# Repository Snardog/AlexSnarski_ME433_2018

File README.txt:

Alex Snarski
3/28/17
Hello World!

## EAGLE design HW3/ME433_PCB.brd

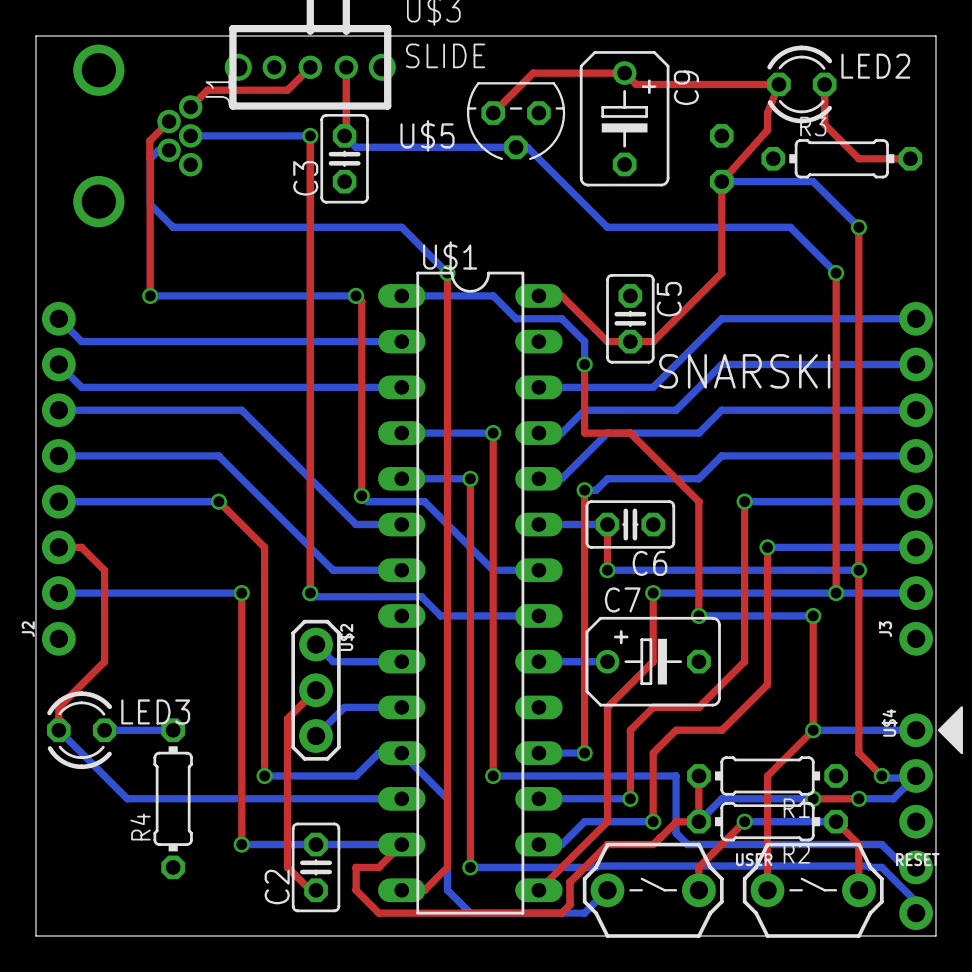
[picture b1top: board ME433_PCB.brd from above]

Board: 2 copper layers, 50.0 x 50.0 mm, 23 parts (1 on the bottom side), 27 nets.

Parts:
C2, C3, C4, C5, C6: 0.1uF; C025-025X050
C7, C9: 10uF; B45181B
J1: USB-MB-H
J2, J3: 1X08
LED2: RED; LED3MM
LED3: GREEN; LED3MM
R1, R2: 10k; 0204/7
R3, R4: 330; 0204/7
RESET: PB
U$1: PIC32; DIL28-3
U$2: OSC
U$3: SLIDE
U$4: PICKIT; 1X05
U$5: MCP1702; TO92
USER: PB

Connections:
+3V3: C2.2, C4.2, C5.2, C6.2, C9.+, J2.2, LED2.A, R1.2, R2.2, U$1.13, U$1.23, U$1.28, U$4.2, U$5.3
+5V: C3.2, J3.2, U$1.15, U$3.3, U$5.2
A0: J2.8, U$1.2
A1: J2.7, U$1.3
A4/LED: J2.3, LED3.A, U$1.12
B2: J2.6, U$1.6
B3: J2.5, U$1.7
B4/USER: J2.4, U$1.11, USER.1
B7: J3.3, U$1.16
B8: J3.4, U$1.17
B9: J3.5, U$1.18
B13: J3.6, U$1.24
B14: J3.7, U$1.25
B15: J3.8, U$1.26
D+/B10: J1.D+, U$1.21
D-/B11: J1.D-, U$1.22
GND: C2.1, C3.1, C4.1, C5.1, C6.1, C7.-, C9.-, J1.GND, J2.1, J3.1, R1.1, R2.1, R3.1, R4.1, RESET.2, U$1.8, U$1.19, U$1.27, U$2.2, U$4.3, U$5.1, USER.2
ID/B5: J1.ID, U$1.14
MCLR: RESET.1, U$1.1, U$4.1
unnamed: LED2.K, R3.2
unnamed: J1.VBUS, U$3.2
unnamed: LED3.K, R4.2
unnamed: C7.+, U$1.20
OCS1: U$1.9, U$2.1
OCS2: U$1.10, U$2.3
PGEC: U$1.5, U$4.5
PGED: U$1.4, U$4.4

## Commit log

2017-03-29 :neckbeard: Added .gitattributes & .gitignore files
2017-03-29 Read me file
    My first commit!
2017-03-29 Added a new line
2017-03-29 Homework 1 Code
    Programming the PIC32 to blink an LED
2017-03-29 Added lines to initialize A4 and B4
2017-03-30 Changed values for config
    Orginally tried to se the bits, changed to things like OFF and ON etc
2017-03-30 Fixed some minor problems with the
2017-03-30 3.3V with no Capacitors
2017-03-30 Added Circuit diagram
2017-03-30 Picture of breadboard
2017-04-04 Added homework 2
2017-04-07 Added homework 3
2017-04-07 Homework 4 started
2017-04-07 Made waveform functions and started initializing pins
2017-04-10 HW 4 progress
2017-04-10 Added proper headers
2017-04-11 more hw 4
2017-04-11 Progress on sending data
2017-04-11 More work on sending data
2017-04-11 Fixed communication
2017-04-11 Communication working, just need to fix the frequencies of the waves
2017-04-12 Finished homework 4
2017-04-12 Started homework 5, created header files
2017-04-12 Added expander functions and read/write functions
2017-04-13 Read function working, need to fix write function
2017-04-14 More work on trying to get the write command working
2017-04-14 More work still, ended up breaking the whole circuit somehow
2017-04-16 Fixed the errors, finally got it to work
2017-04-16 Added video and circuit diagram
2017-04-16 Started homework 6
2017-04-17 Finished HW6
    Only 1 commit along the way because everything worked the first try
2017-04-20 Started homework 7
    Initialized registers
2017-04-26 Finished homework 7
2017-04-26 Started config
2017-05-01 Finished homework 8, started homework 9
    Forgot to commit a few times
2017-05-01 Something broke
2017-05-04 Finished homework 9
2017-05-17 Added Homework 10, started homework 14
    Homework 12 and 13 are also finished, I just need to upload them from my
    desktop
2017-05-17 Homework 12 and 13
2017-05-22 Finished Homework 11
2017-05-22 Finished Homework 15
2017-06-02 Added android usb
2017-06-11 Added the final assignments
